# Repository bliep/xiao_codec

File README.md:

# xiao_codec
Audio codec shield for the Seeed xiao-ble (https://wiki.seeedstudio.com/XIAO_BLE/).
The audio codec is a AIC3254 (https://www.ti.com/product/TLV320AIC3254).

# audio IO
The shield has header pins that directly connects to the audio IO pins of the codec. For connecting to headphones or analog microphones see the application note of the codec (https://www.ti.com/lit/ug/slau497a/slau497a.pdf?ts=1724654493899&ref_url=https%253A%252F%252Fwww.google.com%252F). I.e. if you want to drive headphones, place series capacitors (47u) on the headphone pins to remove the DC.

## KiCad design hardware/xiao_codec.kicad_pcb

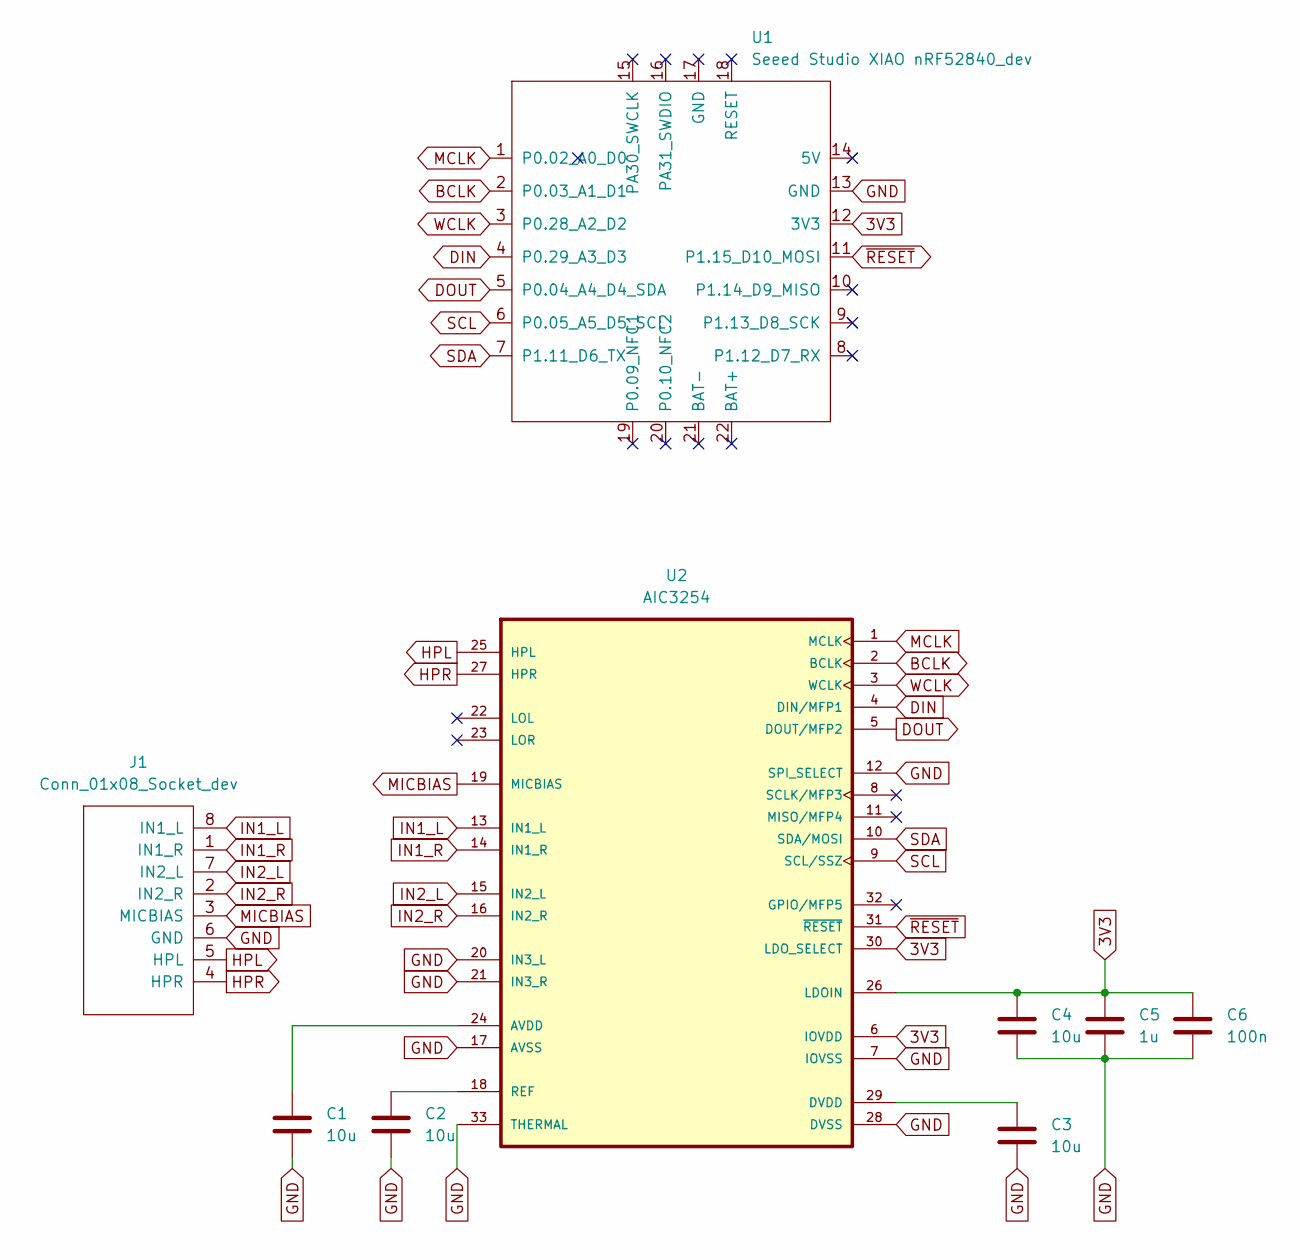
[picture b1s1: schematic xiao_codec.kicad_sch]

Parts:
C1, C2, C3, C4: 10u; C_0805_2012Metric_Pad1.18x1.45mm_HandSolder
C5: 1u; C_0805_2012Metric_Pad1.18x1.45mm_HandSolder
C6: 100n; C_0805_2012Metric_Pad1.18x1.45mm_HandSolder
J1: Conn_01x08_Socket_dev; Conn_8_dev
U1: Seeed Studio XIAO nRF52840_dev; XIAO-Generic-Thruhole-14P-2.54-21X17.8MM_dev
U2: AIC3254; VQFN-32-1EP_5x5mm_P0.5mm_EP3.1x3.1mm_ThermalVias

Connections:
3V3: C4.2, C5.2, C6.2, U1.12 (3V3), U2.6 (IOVDD), U2.26 (LDOIN), U2.30 (LDO_SELECT)
BCLK: U1.2 (P0.03_A1_D1), U2.2 (BCLK)
DIN: U1.4 (P0.29_A3_D3), U2.4 (DIN/MFP1)
DOUT: U1.5 (P0.04_A4_D4_SDA), U2.5 (DOUT/MFP2)
GND: C1.1, C2.1, C3.1, C4.1, C5.1, C6.1, J1.6 (GND), U1.13 (GND), U2.7 (IOVSS), U2.12 (SPI_SELECT), U2.17 (AVSS), U2.20 (IN3_L), U2.21 (IN3_R), U2.28 (DVSS), U2.33 (THERMAL)
HPL: J1.5 (HPL), U2.25 (HPL)
HPR: J1.4 (HPR), U2.27 (HPR)
IN1_L: J1.8 (IN1_L), U2.13 (IN1_L)
IN1_R: J1.1 (IN1_R), U2.14 (IN1_R)
IN2_L: J1.7 (IN2_L), U2.15 (IN2_L)
IN2_R: J1.2 (IN2_R), U2.16 (IN2_R)
MCLK: U1.1 (P0.02_A0_D0), U2.1 (MCLK)
MICBIAS: J1.3 (MICBIAS), U2.19 (MICBIAS)
unnamed: C1.2, U2.24 (AVDD)
unnamed: C3.2, U2.29 (DVDD)
unnamed: C2.2, U2.18 (REF)
SCL: U1.6 (P0.05_A5_D5_SCL), U2.9 (SCL/SSZ)
SDA: U1.7 (P1.11_D6_TX), U2.10 (SDA/MOSI)
WCLK: U1.3 (P0.28_A2_D2), U2.3 (WCLK)
~RESET: U1.11 (P1.15_D10_MOSI), U2.31 (~RESET)

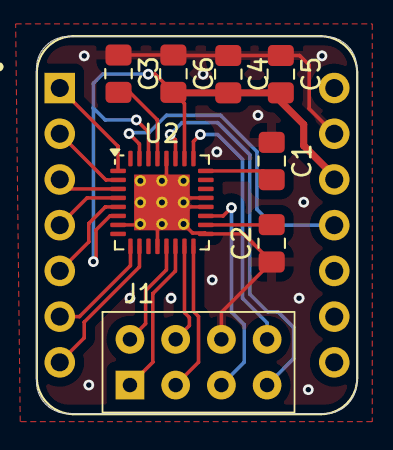
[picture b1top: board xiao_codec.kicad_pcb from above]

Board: 2 copper layers, 17.8 x 21.0 mm, 9 parts (0 on the bottom side), 20 nets.

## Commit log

2024-08-26 Schematics and PCB
2024-08-26 Add schematics PDF
2024-08-26 image of populated PCB
